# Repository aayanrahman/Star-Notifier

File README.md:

# Star Notifier

A small star-shaped USB-C board that lights up when Claude Code or Cursor finishes a task.

- ESP32-C3-WROOM-02 with native USB serial
- 10× WS2812B-2020 LEDs, driven through a 74AHCT1G125 level shifter
- USB-C power (5.1k CC pull-downs, 500 mA polyfuse, USBLC6 ESD), AP2112K 3.3 V regulator
- 0603 passives, 2 layers

Status: schematic done (ERC clean). PCB, firmware and the hook are next.

Made in KiCad 10.

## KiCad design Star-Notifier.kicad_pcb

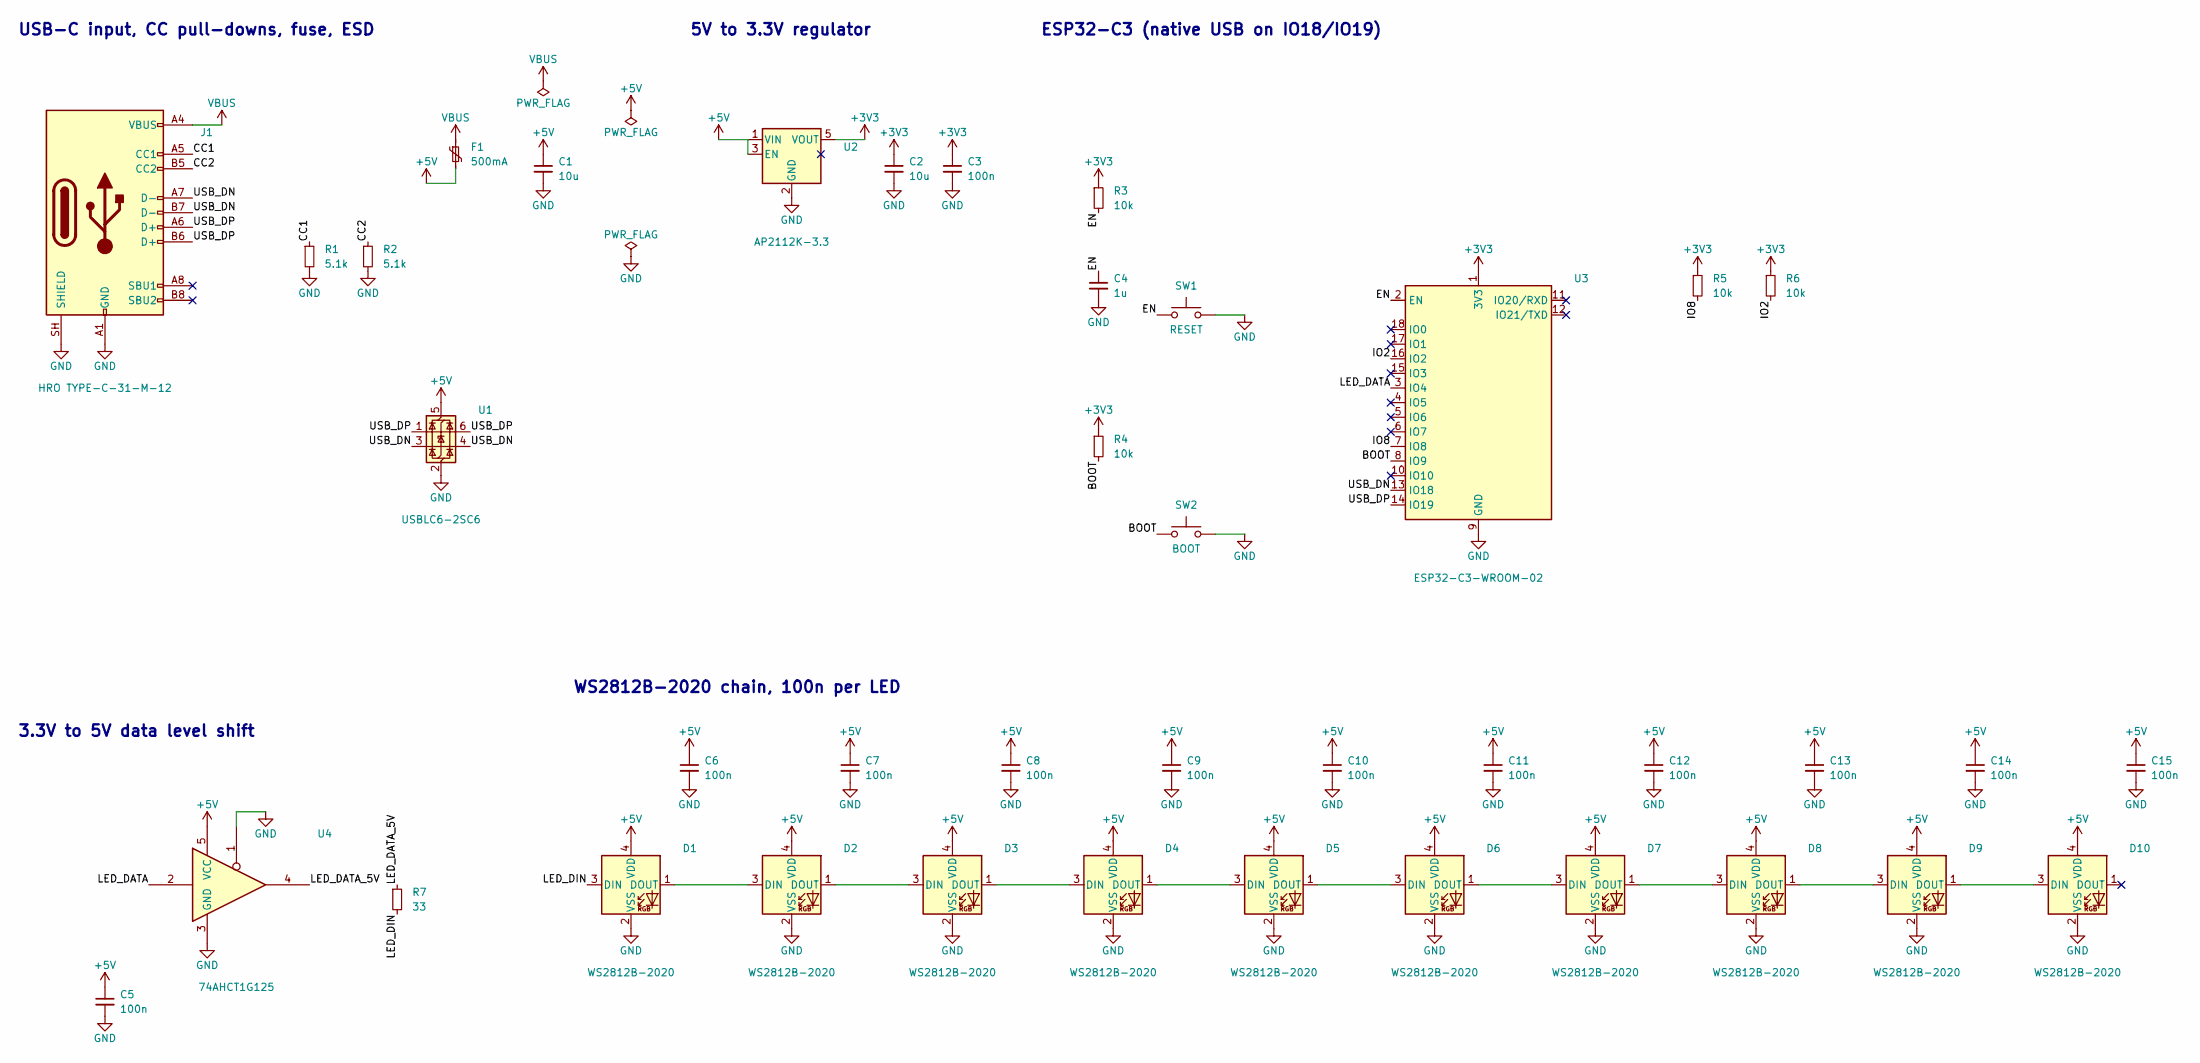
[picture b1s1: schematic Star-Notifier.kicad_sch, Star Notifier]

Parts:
C1, C2: 10u; C_0805_2012Metric
C3, C5, C6, C7, C8, C9, C10, C11, C12, C13, C14, C15: 100n; C_0603_1608Metric
C4: 1u; C_0603_1608Metric
D1, D2, D3, D4, D5, D6, D7, D8, D9, D10: WS2812B-2020; LED_WS2812B-2020_PLCC4_2.0x2.0mm
F1: 500mA; Fuse_1206_3216Metric
J1: HRO TYPE-C-31-M-12; USB_C_Receptacle_HRO_TYPE-C-31-M-12
R1, R2: 5.1k; R_0603_1608Metric
R3, R4, R5, R6: 10k; R_0603_1608Metric
R7: 33; R_0603_1608Metric
SW1: RESET; SW_Push_1P1T_XKB_TS-1187A
SW2: BOOT; SW_Push_1P1T_XKB_TS-1187A
U1: USBLC6-2SC6; SOT-23-6
U2: AP2112K-3.3; SOT-23-5
U3: ESP32-C3-WROOM-02
U4: 74AHCT1G125; SOT-23-5

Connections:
+3V3: C2.1, C3.1, R3.1, R4.1, R5.1, R6.1, U2.5 (VOUT), U3.1 (3V3)
+5V: C1.1, C5.1, C6.1, C7.1, C8.1, C9.1, C10.1, C11.1, C12.1, C13.1, C14.1, C15.1, D1.4 (VDD), D2.4 (VDD), D3.4 (VDD), D4.4 (VDD), D5.4 (VDD), D6.4 (VDD), D7.4 (VDD), D8.4 (VDD), D9.4 (VDD), D10.4 (VDD), F1.2, U1.5 (VBUS), U2.1 (VIN), U2.3 (EN), U4.5 (VCC)
/BOOT: R4.2, SW2.1, U3.8 (IO9)
/CC1: J1.A5 (CC1), R1.1
/CC2: J1.B5 (CC2), R2.1
/EN: C4.1, R3.2, SW1.1, U3.2 (EN)
/IO2: R6.2, U3.16 (IO2)
/IO8: R5.2, U3.7 (IO8)
/LED_DATA: U3.3 (IO4), U4.2
/LED_DATA_5V: R7.1, U4.4
/LED_DIN: D1.3 (DIN), R7.2
/USB_DN: J1.A7 (D-), J1.B7 (D-), U1.3 (I/O2), U1.4 (I/O2), U3.13 (IO18)
/USB_DP: J1.A6 (D+), J1.B6 (D+), U1.1 (I/O1), U1.6 (I/O1), U3.14 (IO19)
GND: C1.2, C2.2, C3.2, C4.2, C5.2, C6.2, C7.2, C8.2, C9.2, C10.2, C11.2, C12.2, C13.2, C14.2, C15.2, D1.2 (VSS), D2.2 (VSS), D3.2 (VSS), D4.2 (VSS), D5.2 (VSS), D6.2 (VSS), D7.2 (VSS), D8.2 (VSS), D9.2 (VSS), D10.2 (VSS), J1.A1 (GND), J1.A12 (GND), J1.B1 (GND), J1.B12 (GND), J1.SH (SHIELD), R1.2, R2.2, SW1.2, SW2.2, U1.2 (GND), U2.2 (GND), U3.9 (GND), U3.19 (GND), U4.1, U4.3 (GND)
unnamed: D1.1 (DOUT), D2.3 (DIN)
unnamed: D2.1 (DOUT), D3.3 (DIN)
unnamed: D3.1 (DOUT), D4.3 (DIN)
unnamed: D4.1 (DOUT), D5.3 (DIN)
unnamed: D5.1 (DOUT), D6.3 (DIN)
unnamed: D6.1 (DOUT), D7.3 (DIN)
unnamed: D7.1 (DOUT), D8.3 (DIN)
unnamed: D8.1 (DOUT), D9.3 (DIN)
unnamed: D9.1 (DOUT), D10.3 (DIN)
VBUS: F1.1, J1.A4 (VBUS), J1.A9 (VBUS), J1.B4 (VBUS), J1.B9 (VBUS)

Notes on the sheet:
WS2812B-2020 chain, 100n per LED
3.3V to 5V data level shift
5V to 3.3V regulator
USB-C input, CC pull-downs, fuse, ESD
ESP32-C3 (native USB on IO18/IO19)

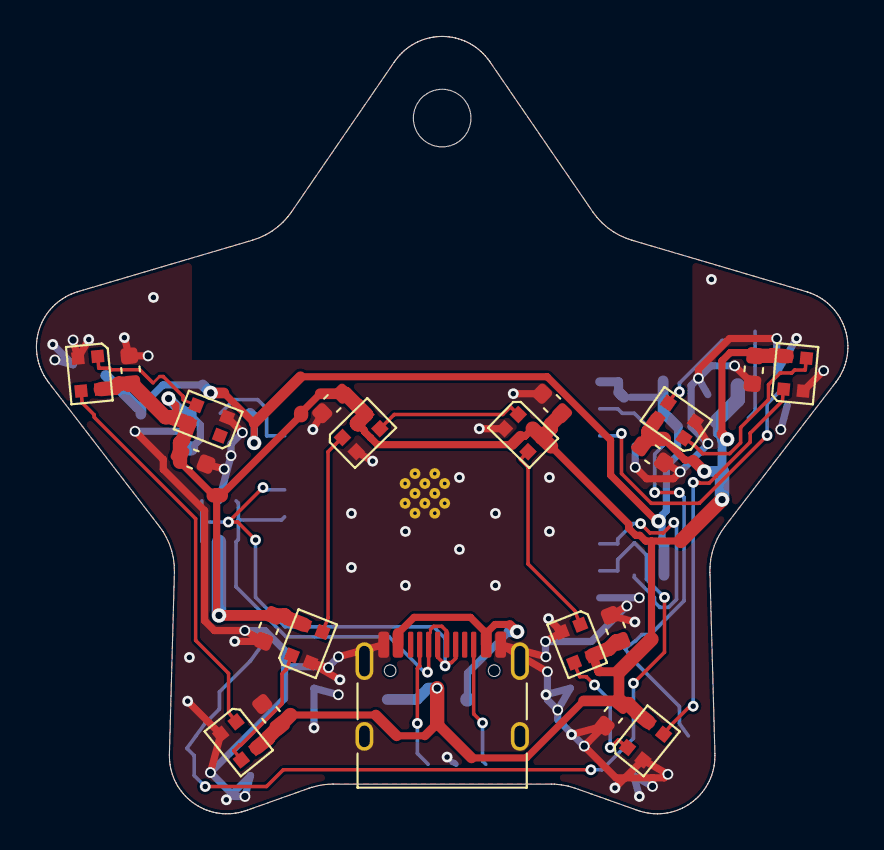
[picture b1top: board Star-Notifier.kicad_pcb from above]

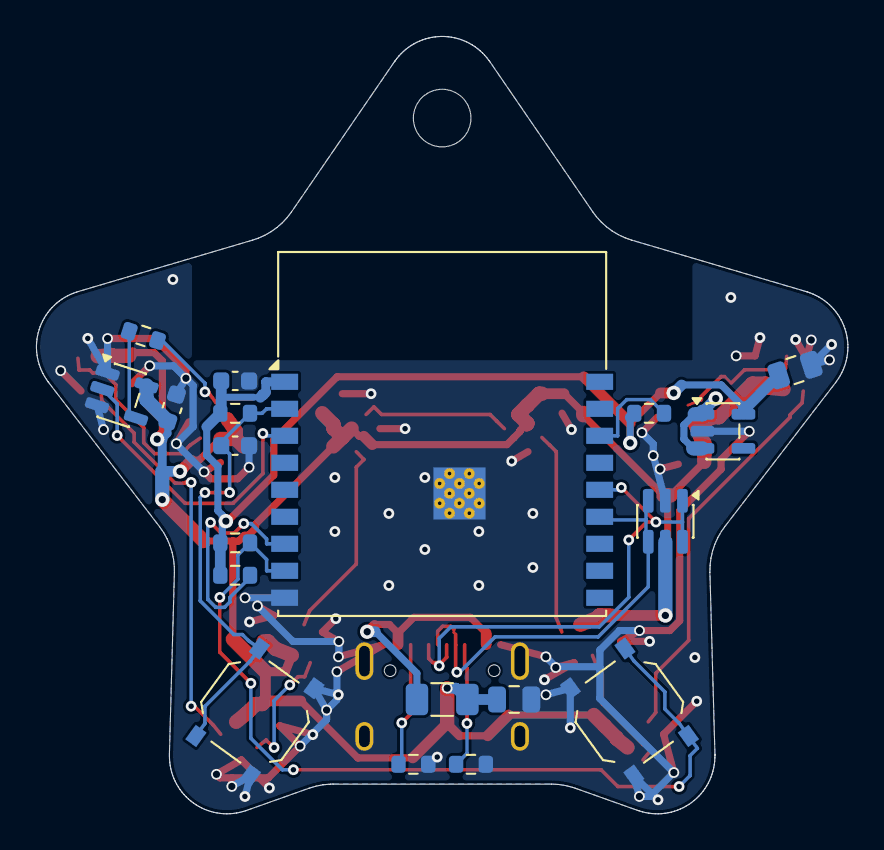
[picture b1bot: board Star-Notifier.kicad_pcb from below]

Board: 2 copper layers, 45.1 x 43.2 mm, 40 parts (19 on the bottom side), 24 nets.
